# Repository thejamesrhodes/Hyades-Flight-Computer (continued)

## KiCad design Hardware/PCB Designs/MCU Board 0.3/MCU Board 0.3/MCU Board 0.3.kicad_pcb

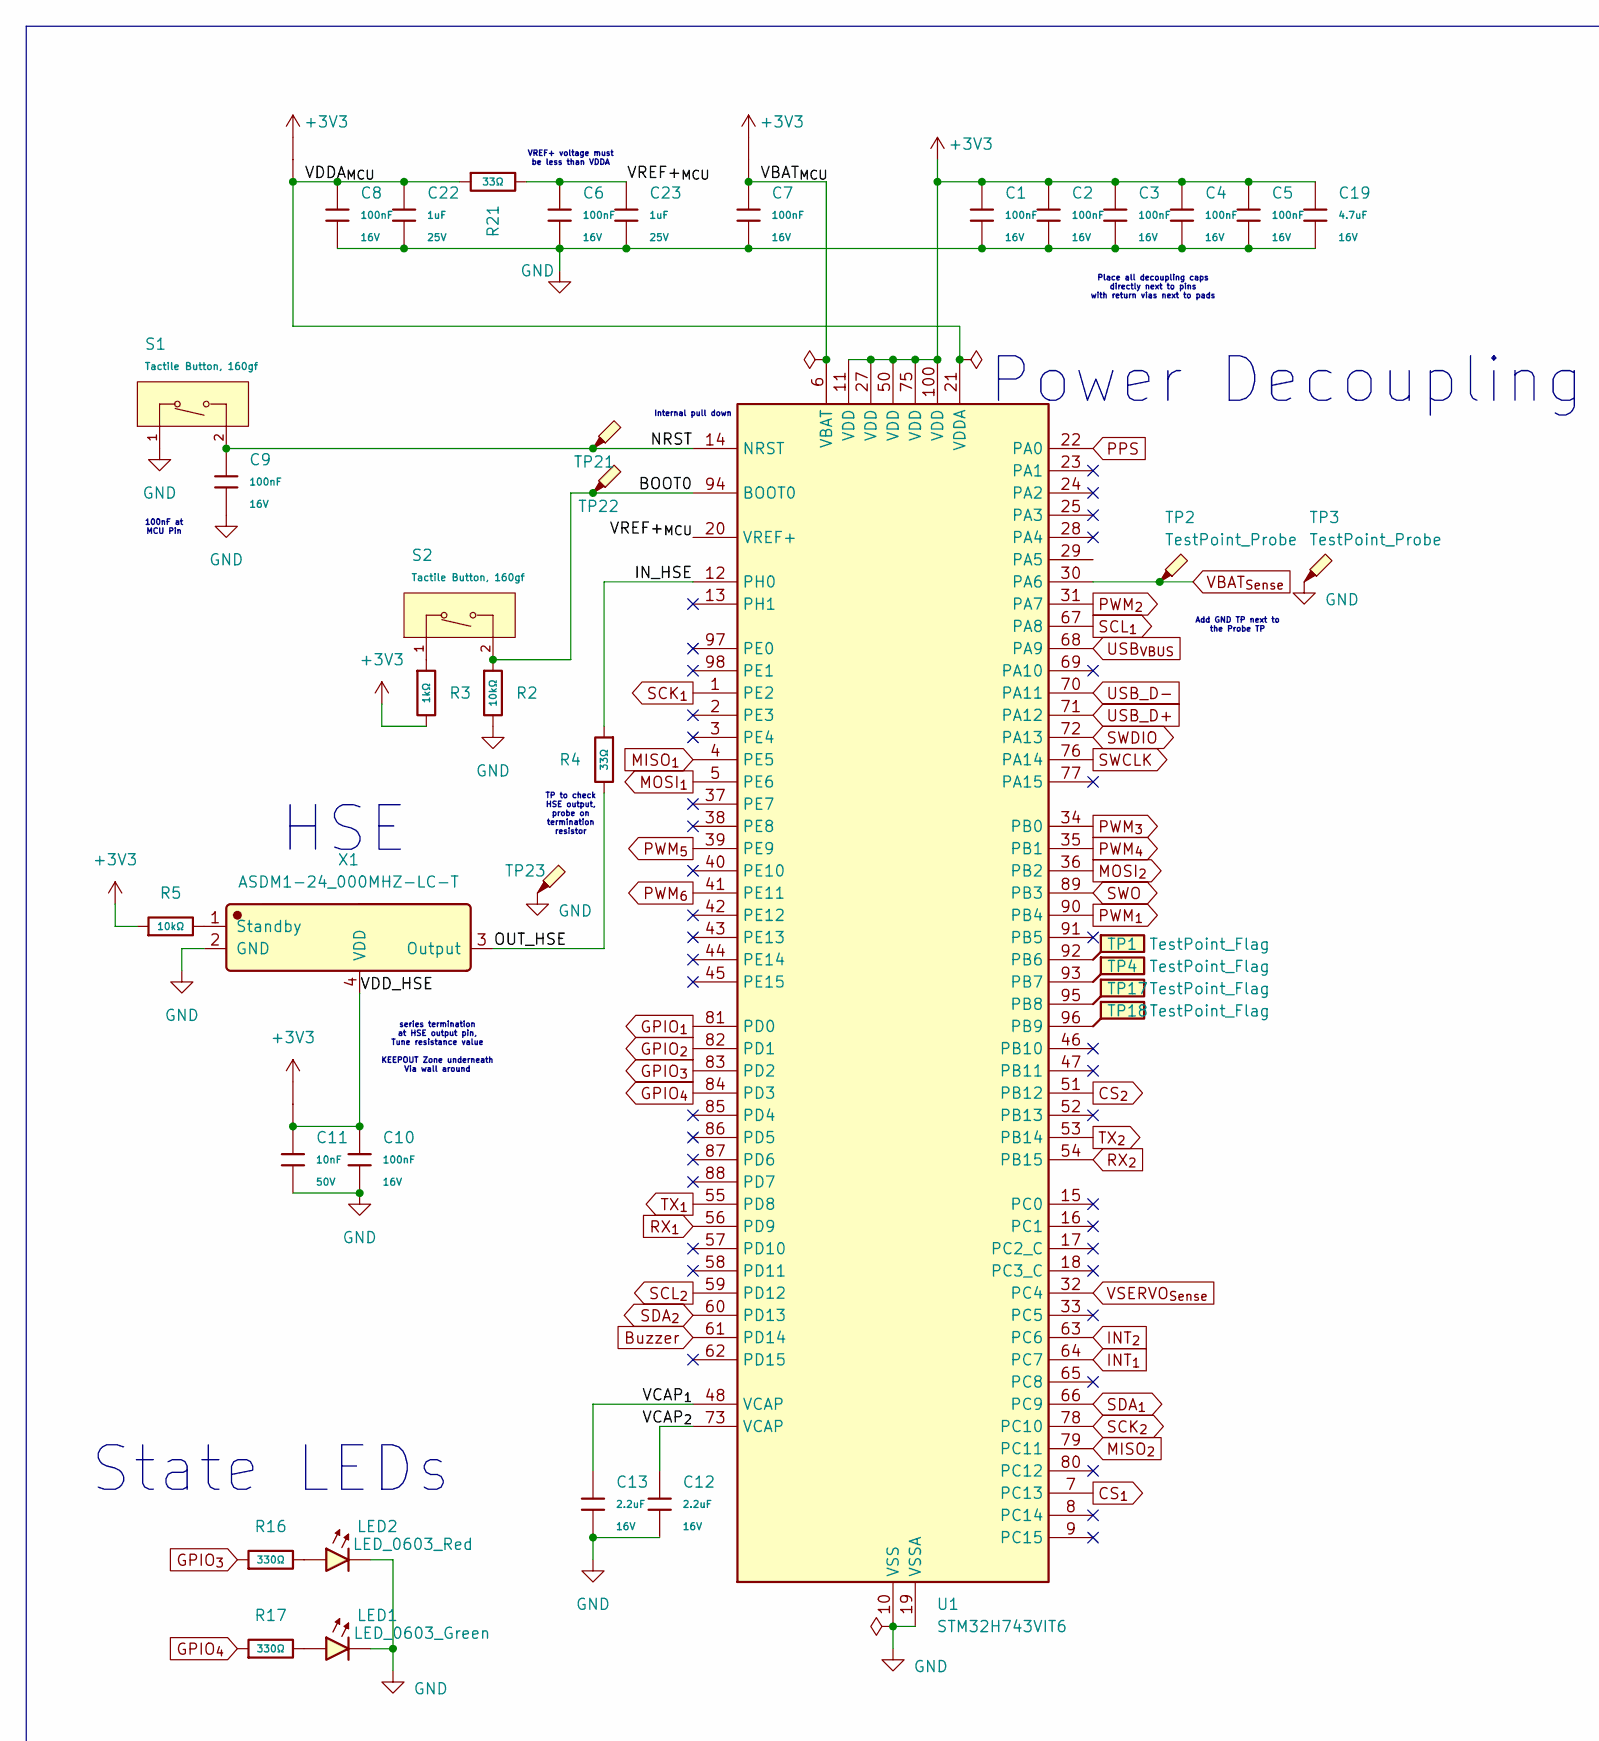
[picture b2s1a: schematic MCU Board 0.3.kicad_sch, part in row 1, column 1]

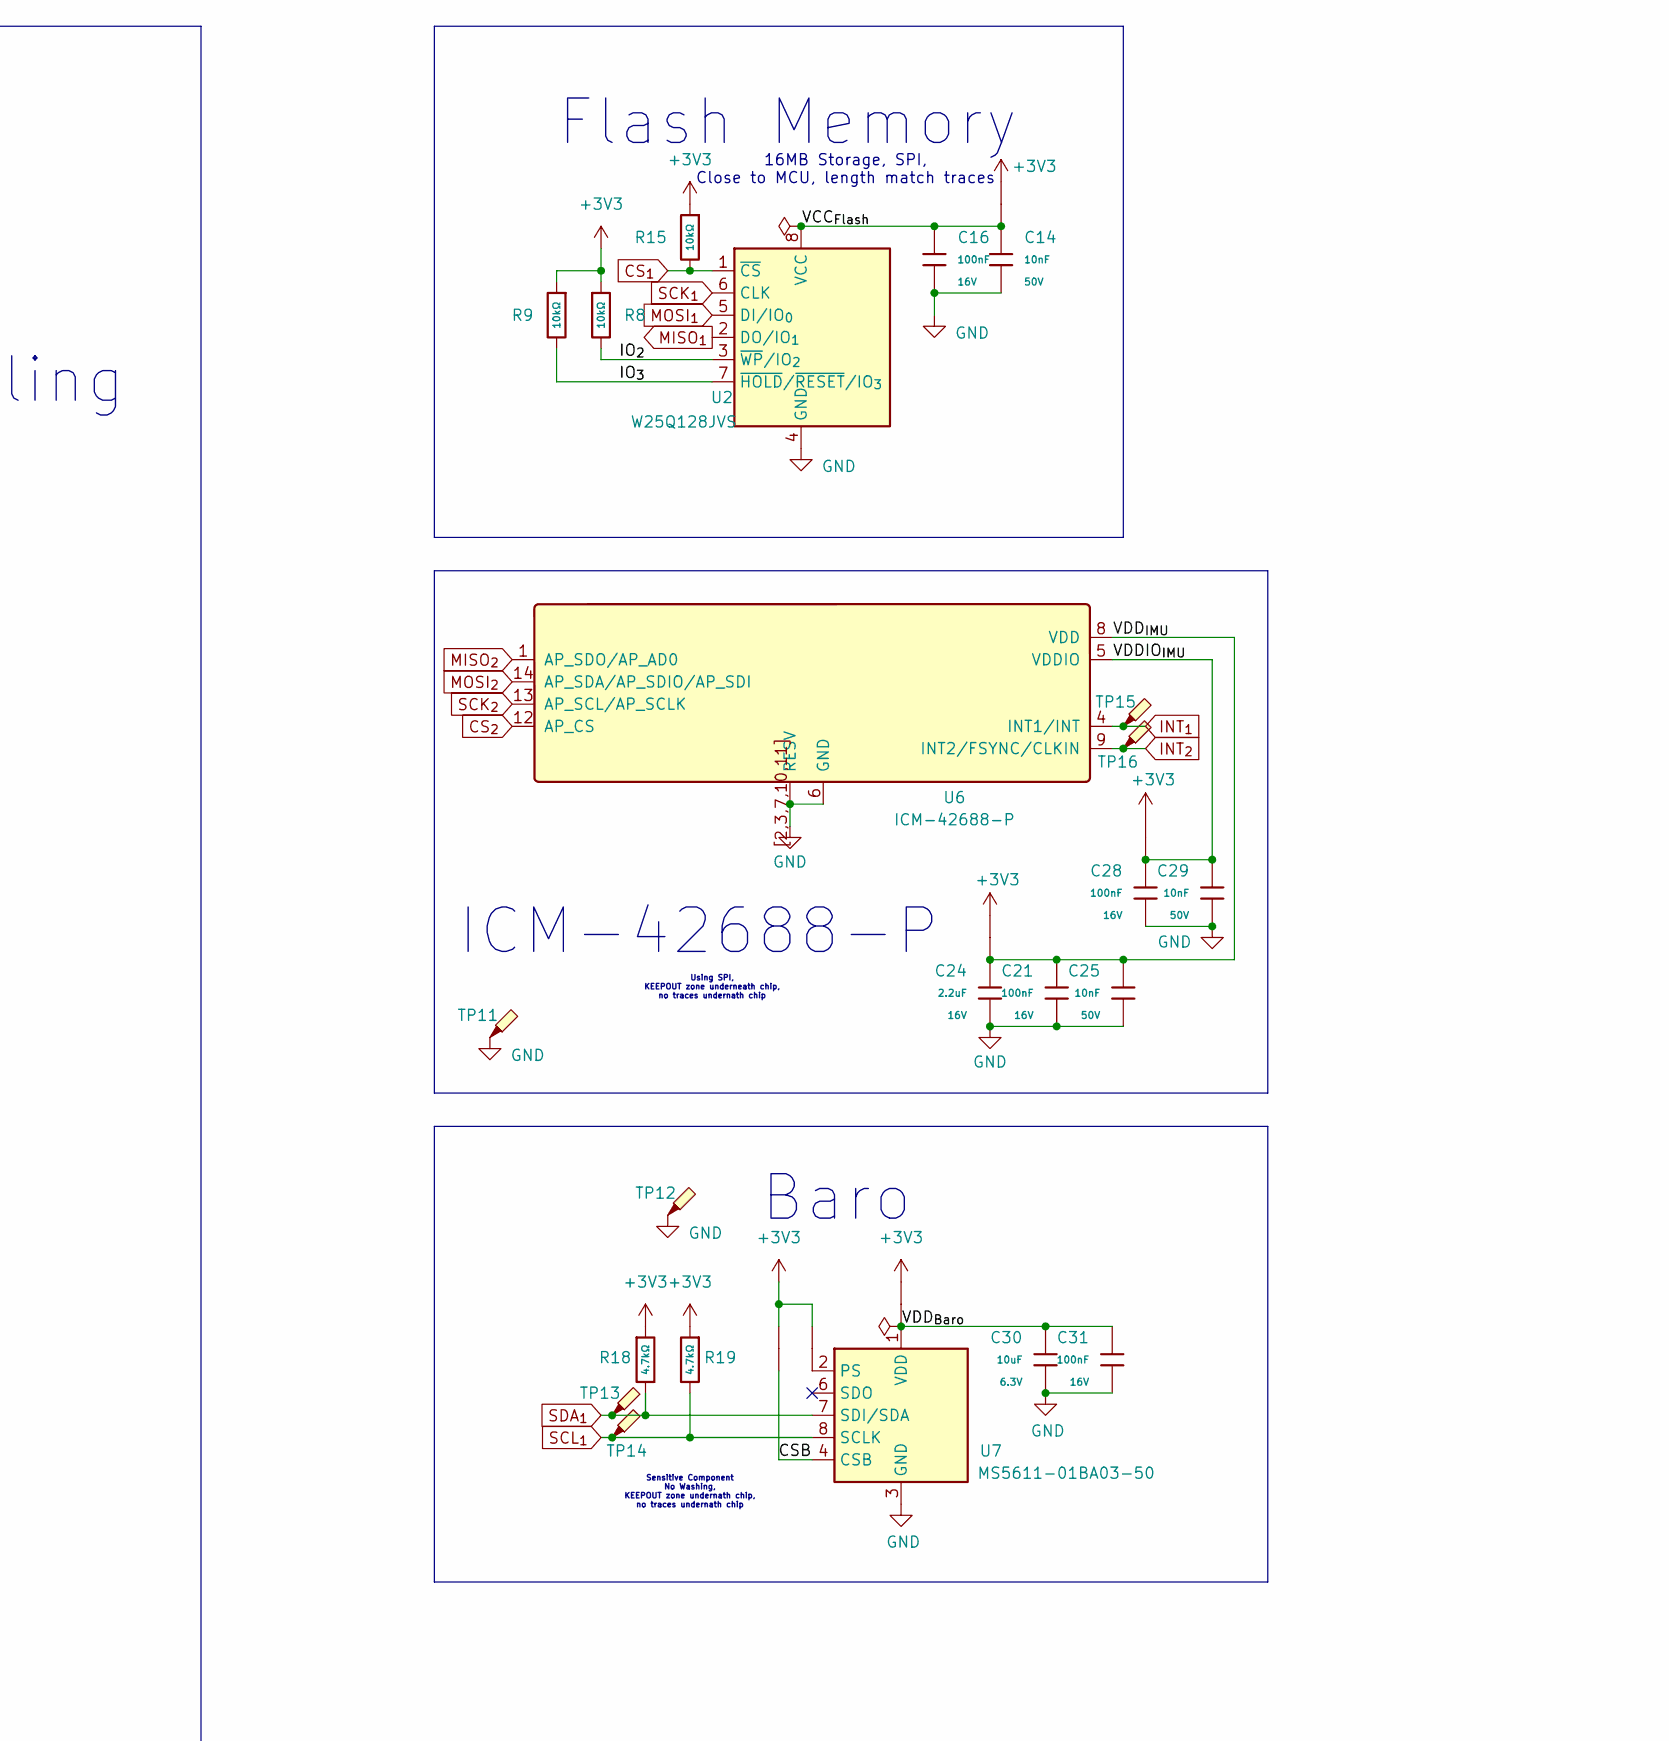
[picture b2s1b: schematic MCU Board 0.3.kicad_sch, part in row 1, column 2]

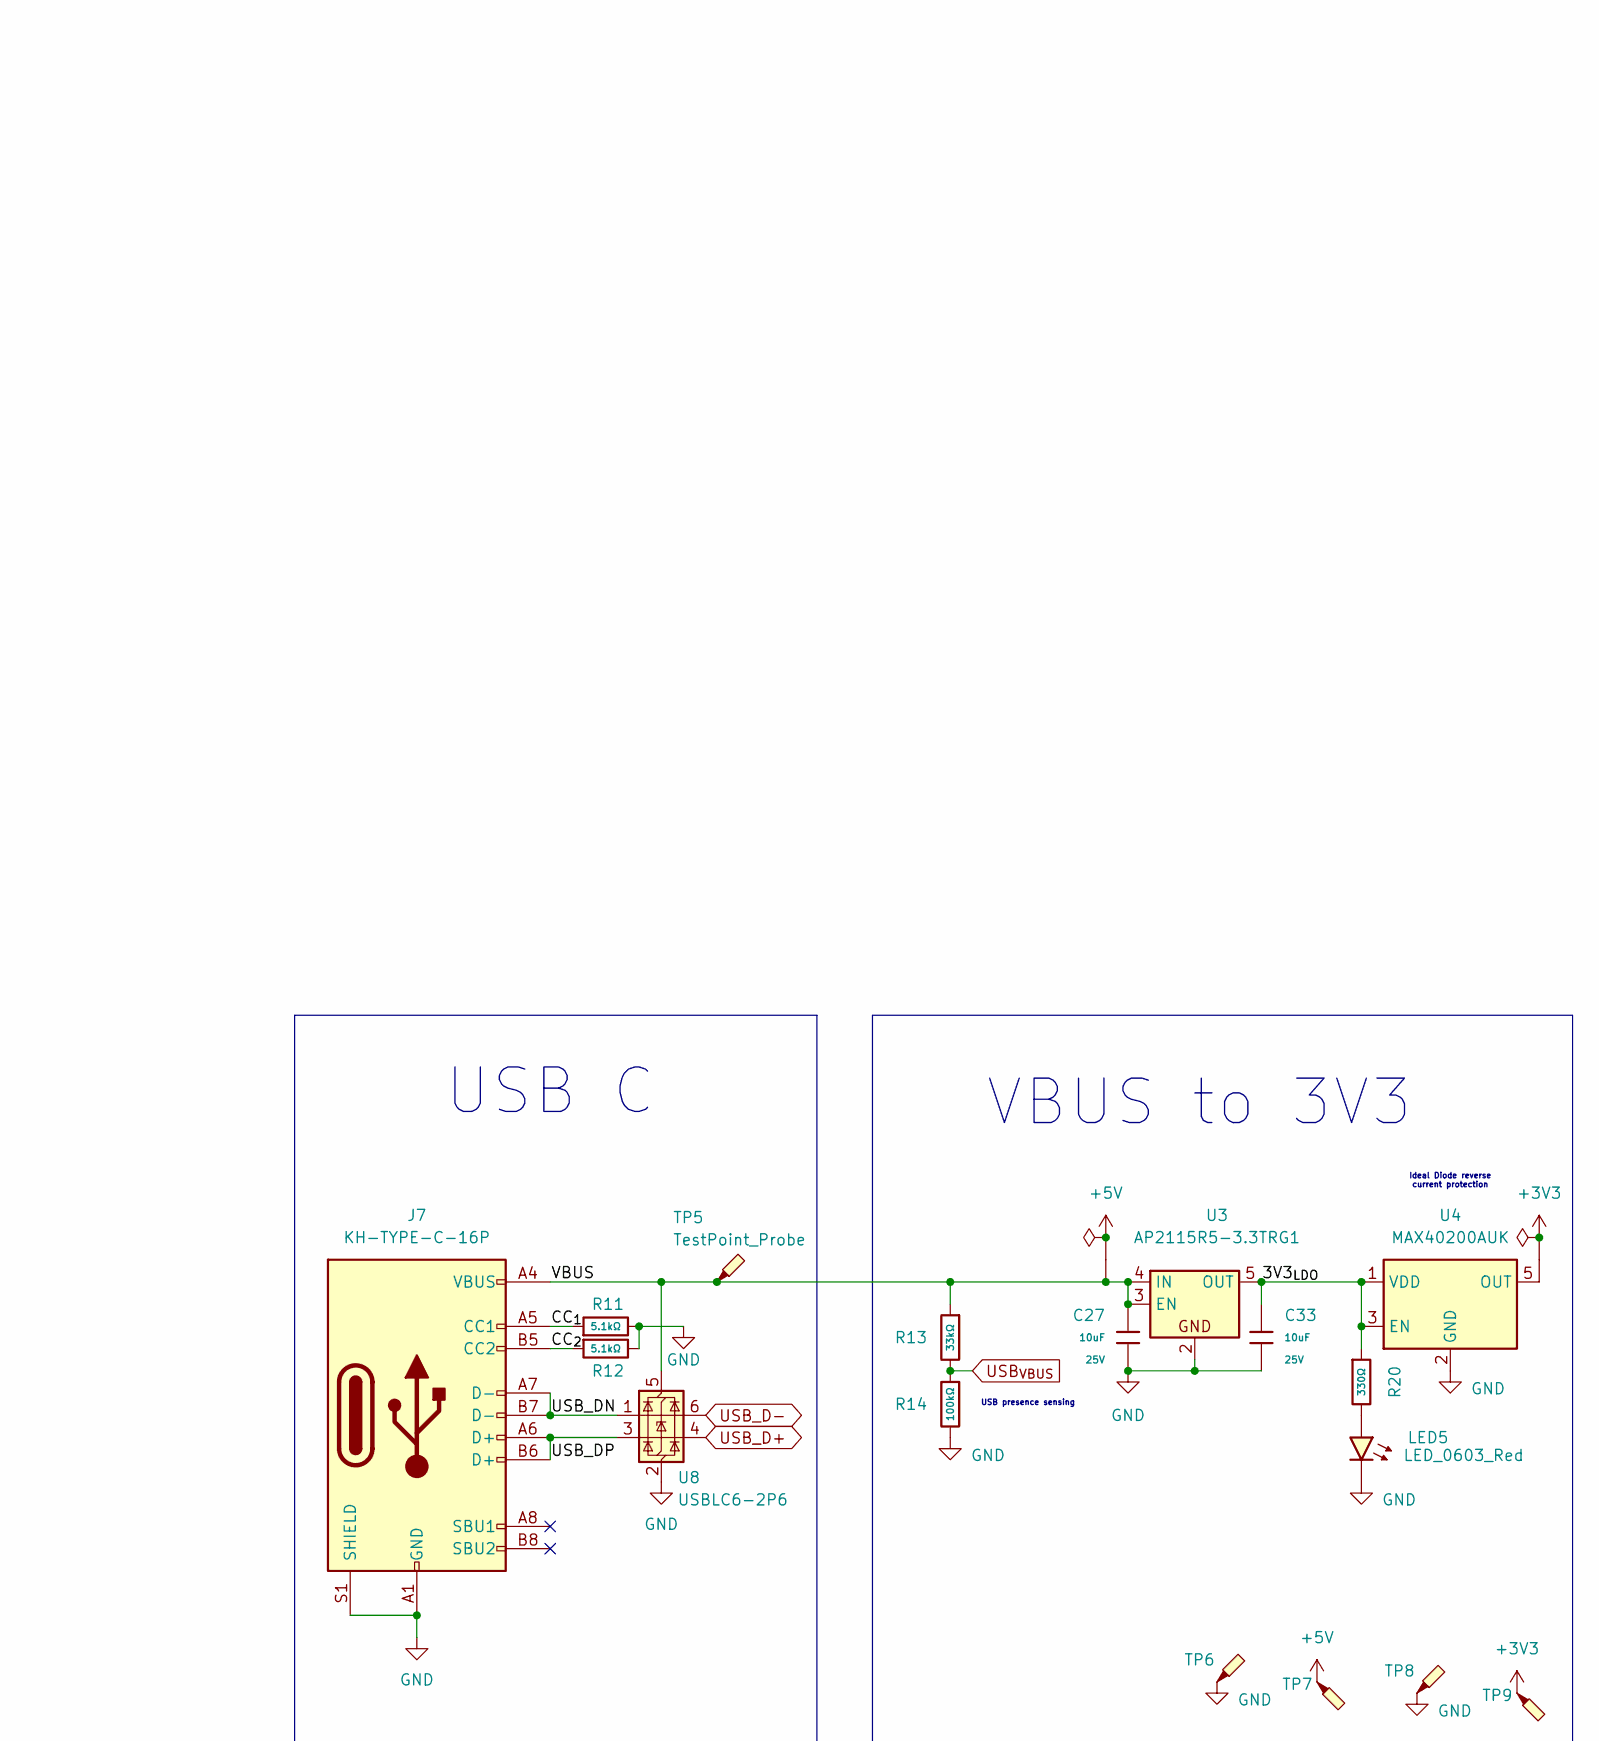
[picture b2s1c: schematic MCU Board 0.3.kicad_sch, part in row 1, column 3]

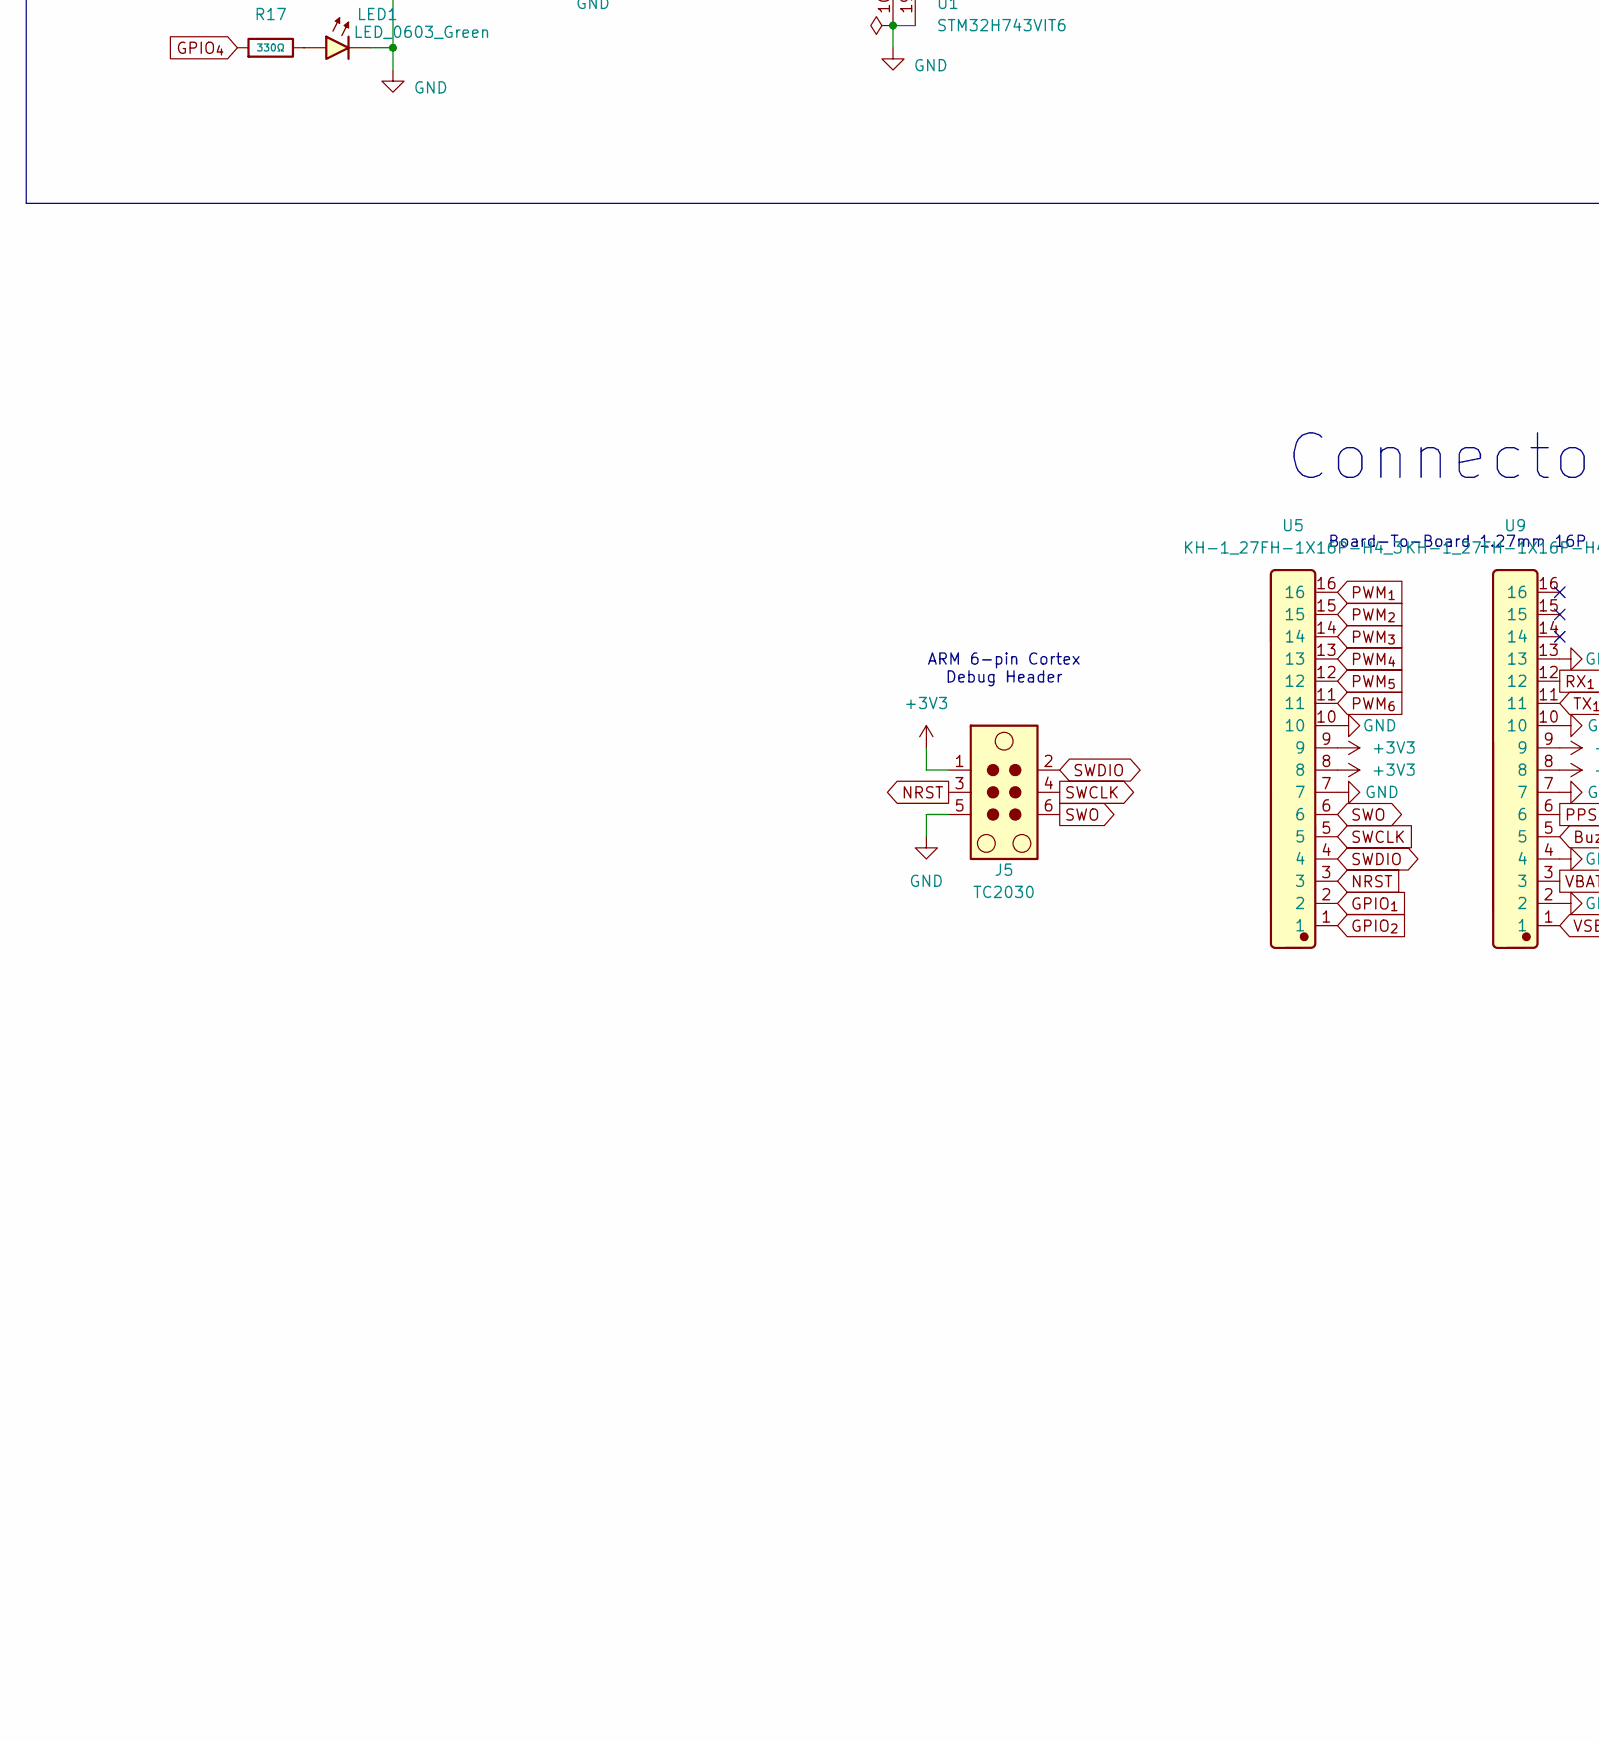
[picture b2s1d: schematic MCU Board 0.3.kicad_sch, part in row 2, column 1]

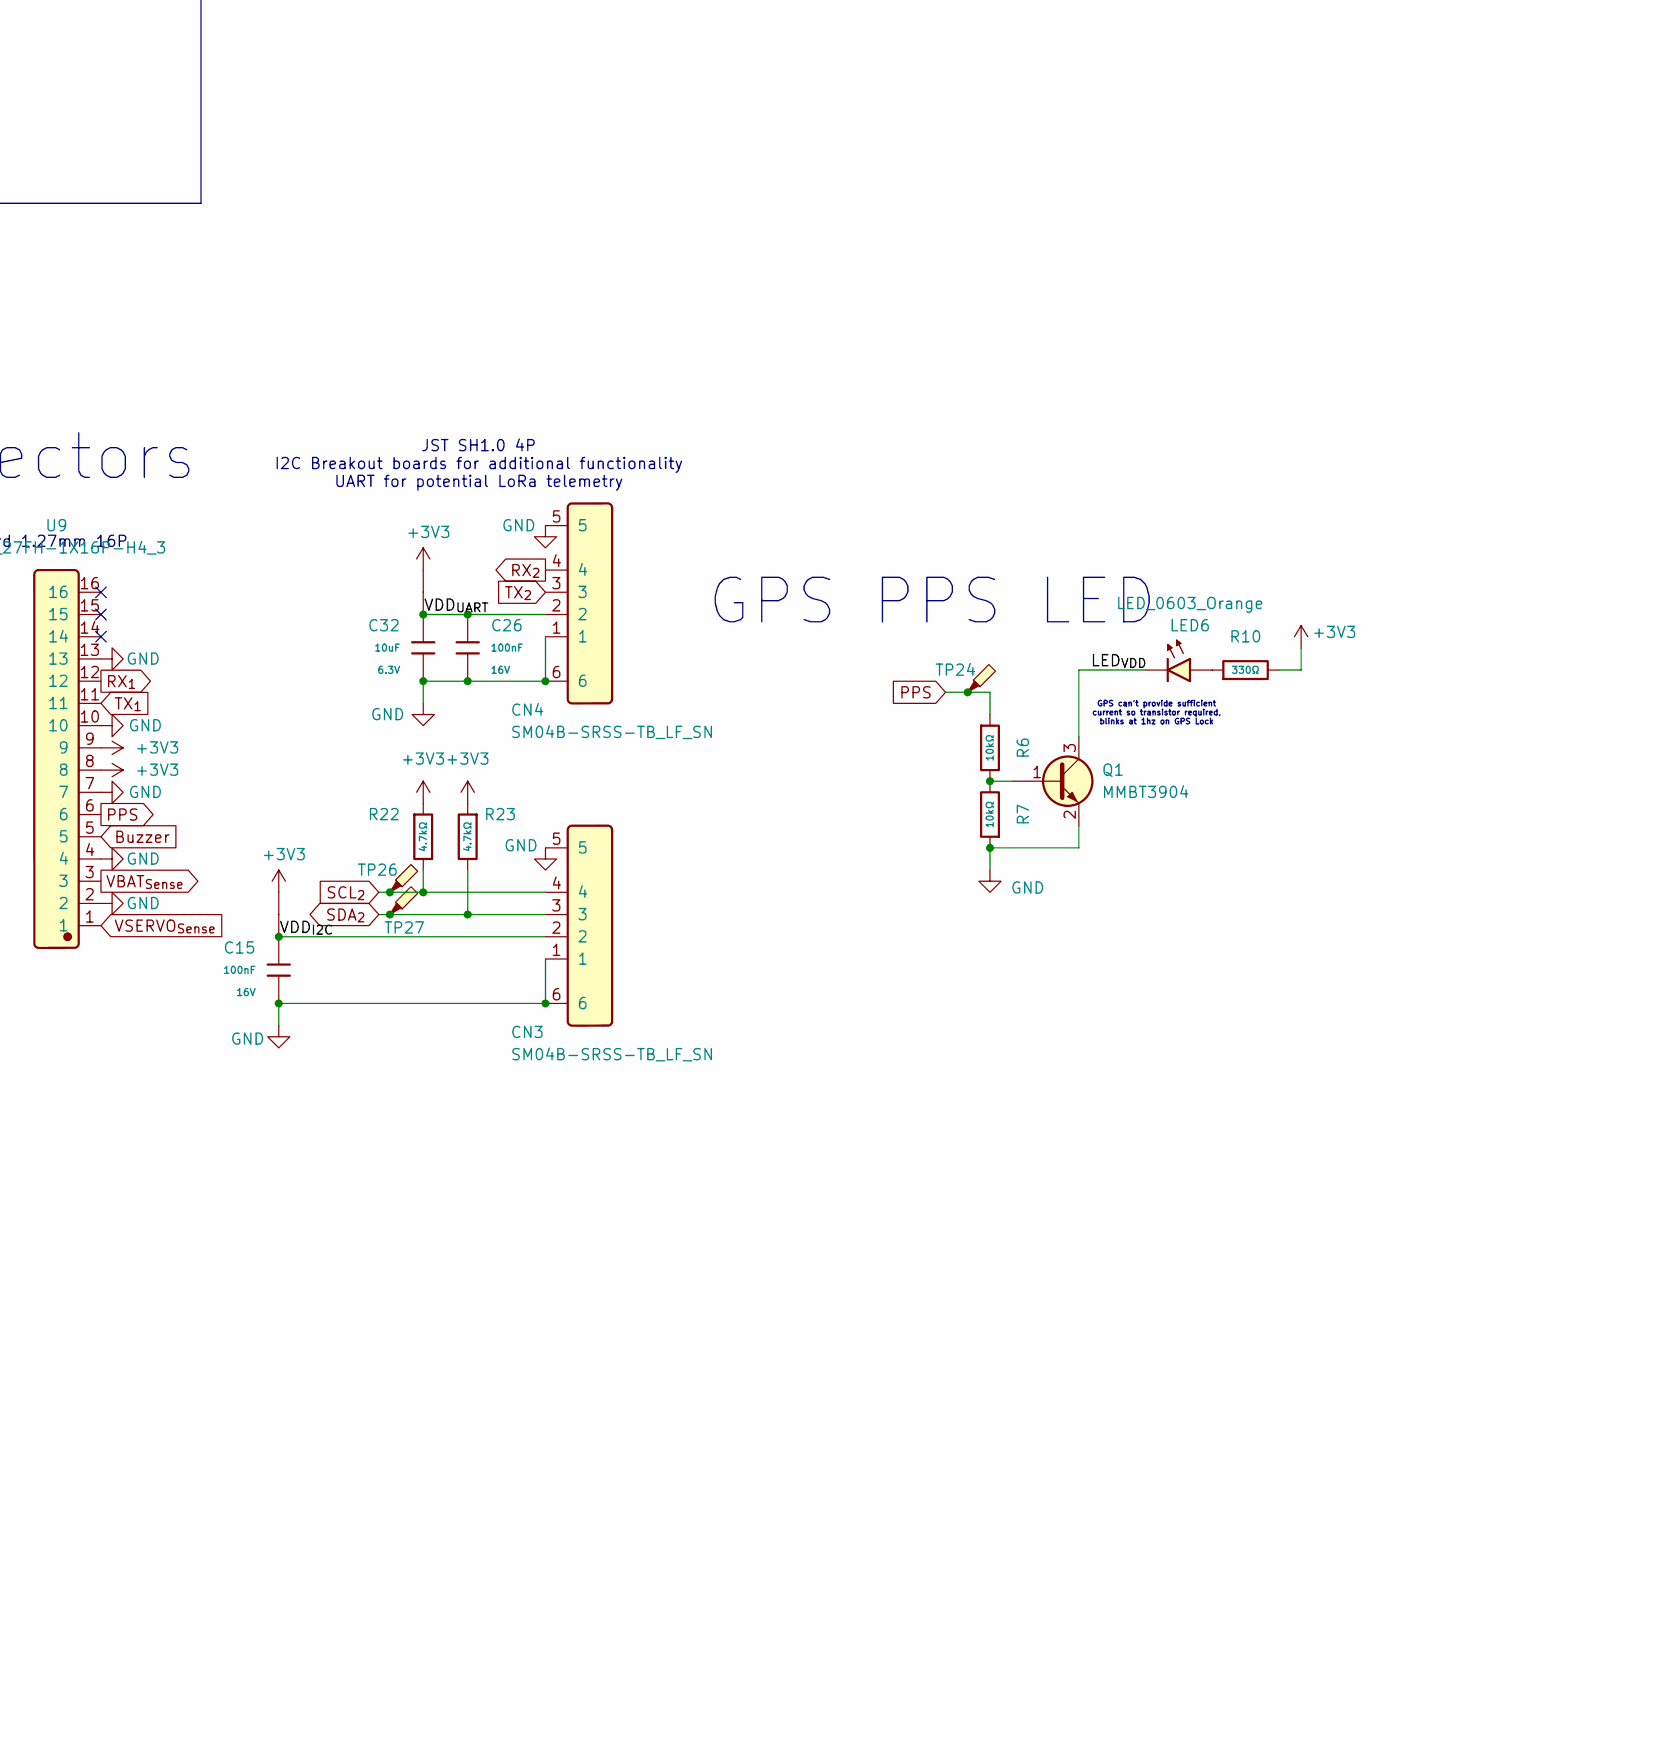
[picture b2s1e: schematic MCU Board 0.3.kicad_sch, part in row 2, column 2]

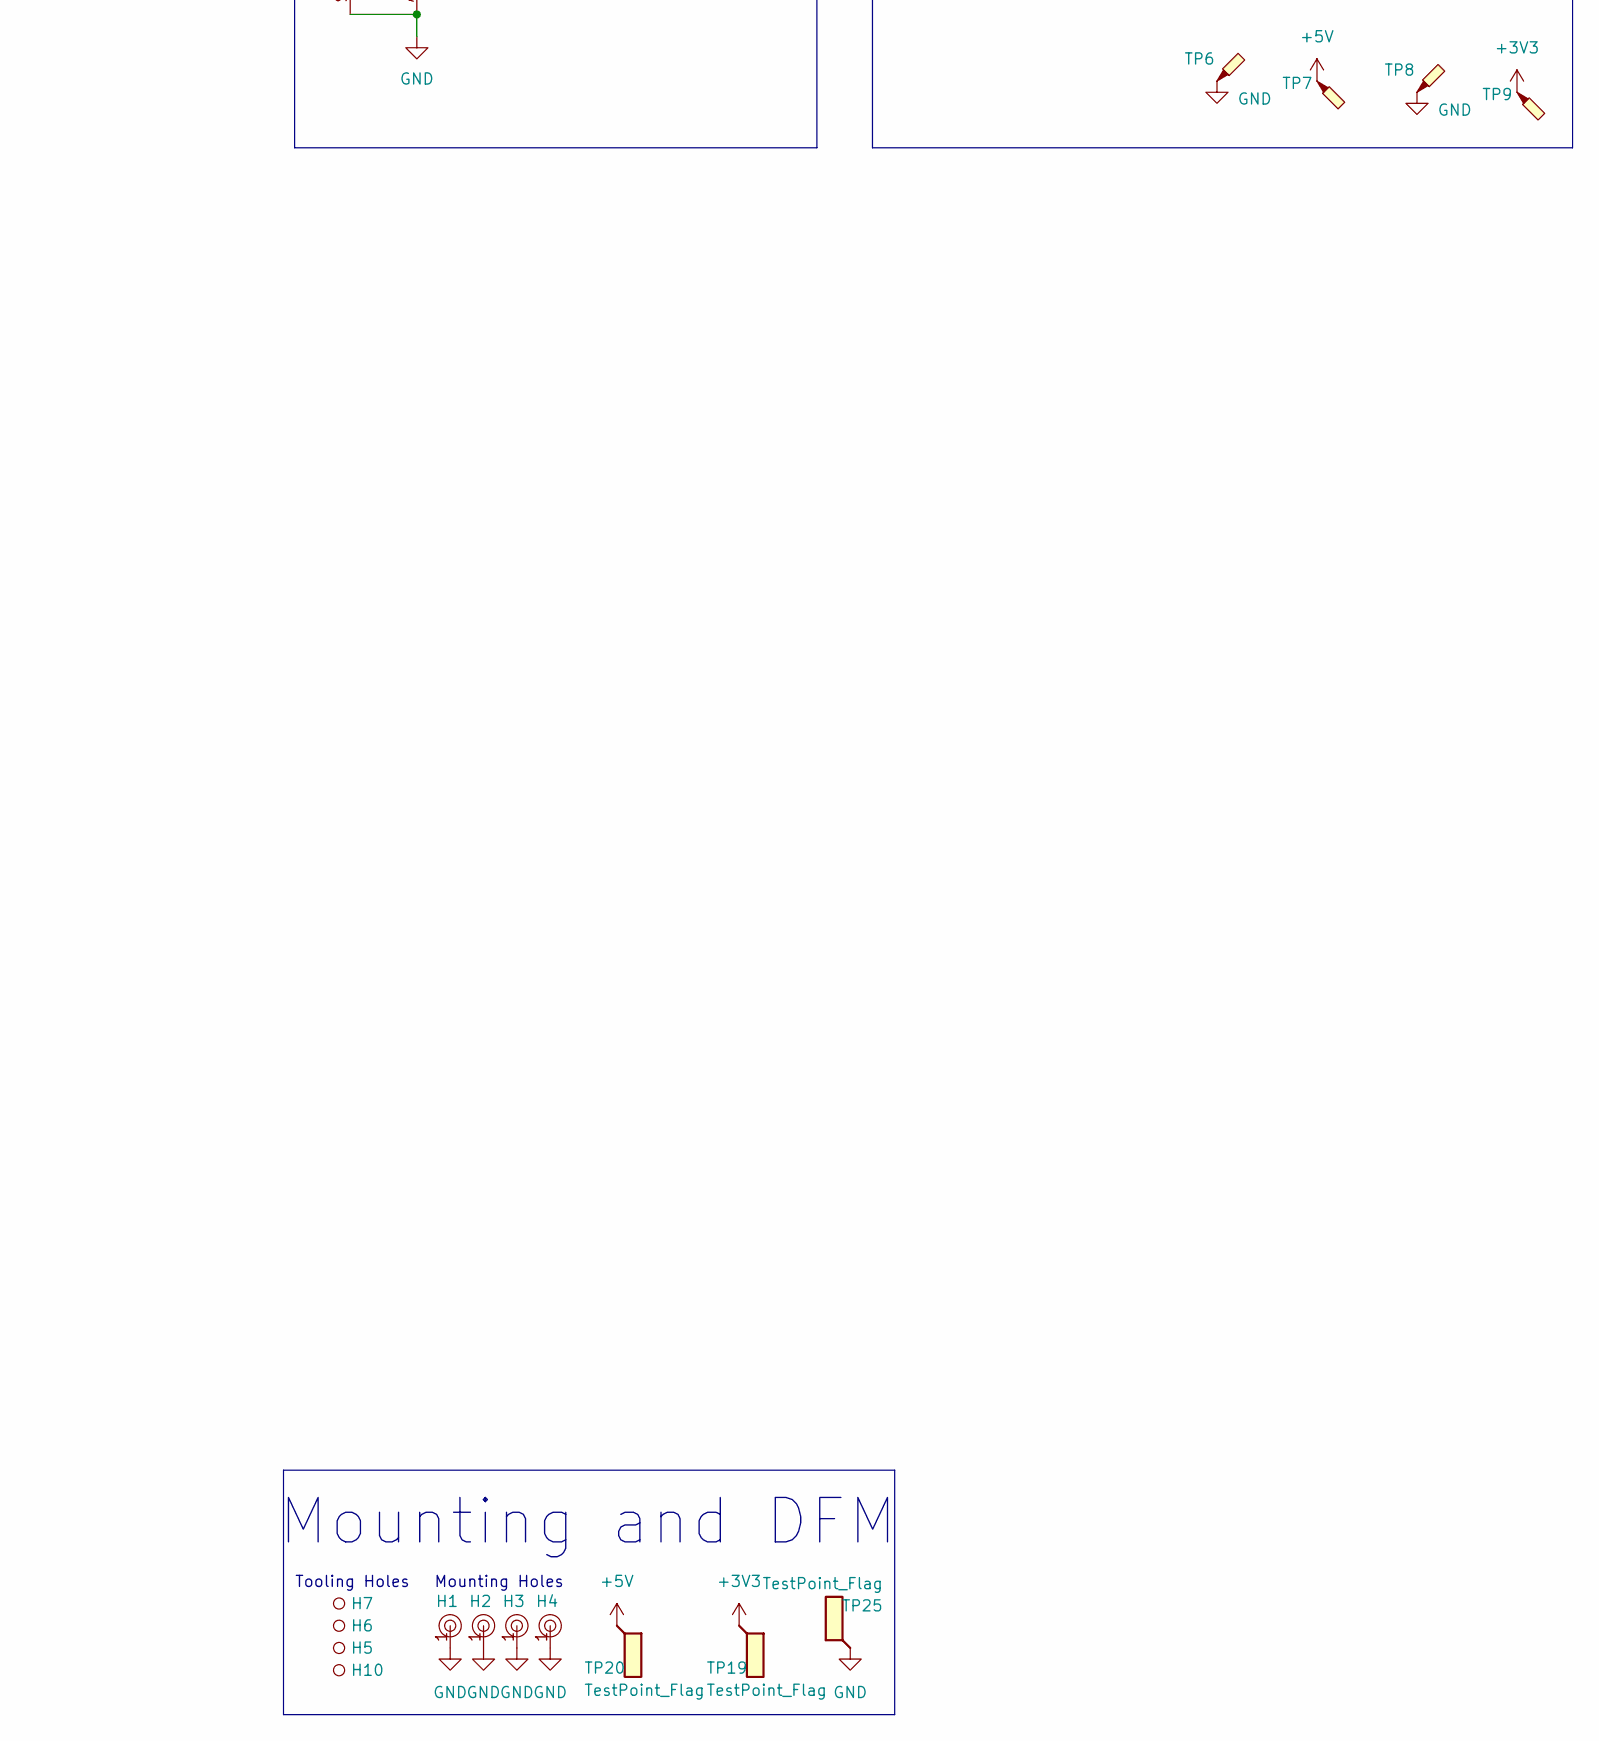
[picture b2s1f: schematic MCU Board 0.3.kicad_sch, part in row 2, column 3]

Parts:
C1, C2, C3, C4, C5, C6, C7, C8, C9, C10, C15, C16, C21, C26, C28, C31: 100nF; C_0402; Voltage Rated 16V; Tolerance ±10%; Part CL05B104KO5NNNC; LCSC C1525
C11, C14, C25, C29: 10nF; C_0402; Voltage Rated 50V; Tolerance ±10%; Part CL05B103KB5NNNC; LCSC C15195
C12, C13, C24: 2.2uF; C_0603; Voltage Rated 16V; Tolerance ±10%; Part CL10A225KO8NNNC; LCSC C23630
C19: 4.7uF; C_0603; Voltage Rated 16V; Tolerance ±10%; Part CL10A475KO8NNNC; LCSC C19666
C22, C23: 1uF; C_0402; Voltage Rated 25V; Tolerance ±10%; Part CL05A105KA5NQNC; LCSC C52923
C27, C33: 10uF; C_0805; Voltage Rated 25V; Tolerance ±10%; Part CL21A106KAYNNNE; LCSC C15850
C30, C32: 10uF; C_0402; Voltage Rated 6.3V; Tolerance ±20%; Part CL05A106MQ5NUNC; LCSC C15525
CN3, CN4: SM04B-SRSS-TB_LF_SN; JST_SH_SM04B-SRSS-TB_1x04-1MP_P1.00mm_Horizontal; Manufacturer Part SM04B-SRSS-TB(LF)(SN); LCSC C160404
H1, H2, H3, H4: Hole, 3mm
H5, H6, H7, H10: Hole_Tooling_JLCPCB
J5: TC2030; Tag-Connect_TC2030-IDC-NL_2x03_P1.27mm_Vertical
J7: KH-TYPE-C-16P; USB_C_Receptacle_GCT_USB4105-xx-A_16P_TopMnt_Horizontal
LED1: LED_0603_Green; LED_0603_1608Metric
LED2, LED5: LED_0603_Red; LED_0603_1608Metric
LED6: LED_0603_Orange; LED_0603_1608Metric
Q1: MMBT3904; SOT-23
R2, R5, R6, R7, R8, R9, R15: 10kΩ; R_0402; Overload Voltage (Max) 50V; Tolerance ±1%; Part 0402WGF1002TCE; LCSC C25744
R3: 1kΩ; R_0402; Overload Voltage (Max) 50V; Tolerance ±1%; Part 0402WGF1001TCE; LCSC C11702
R4, R21: 33Ω; R_0402; Overload Voltage (Max) 50V; Tolerance ±1%; Part 0402WGF330JTCE; LCSC C25105
R10, R16, R17, R20: 330Ω; R_0402; Overload Voltage (Max) 50V; Tolerance ±1%; Part 0402WGF3300TCE; LCSC C25104
R11, R12: 5.1kΩ; R_0402; Overload Voltage (Max) 50V; Tolerance ±1%; Part 0402WGF5101TCE; LCSC C25905
R13: 33kΩ; R_0402; Overload Voltage (Max) 50V; Tolerance ±1%; Part 0402WGF3302TCE; LCSC C25779
R14: 100kΩ; R_0402; Overload Voltage (Max) 50V; Tolerance ±1%; Part 0402WGF1003TCE; LCSC C25741
R18, R19, R22, R23: 4.7kΩ; R_0402; Overload Voltage (Max) 50V; Tolerance ±1%; Part 0402WGF4701TCE; LCSC C25900
S1, S2: Tactile Button, 160gf; SW_TS-1088-AR02016; Voltage Rating (Dc) 12V; Part TS-1088-AR02016; LCSC C720477
TIE1, TIE3, TIE4, TIE5, TIE6, TIE7, TIE8, TIE9, TIE10, TIE11, TIE12, TIE13, TIE14: NetTie; JUMPER_SMD_1x2_tiny_shorted; Part Number Do Not Place
TP1, TP4, TP17, TP18: TestPoint_Flag; TestPoint_Pad_04
TP2, TP3, TP5, TP6, TP7, TP8, TP9, TP11, TP12, TP13, TP14, TP15, TP16, TP21, TP22, TP23, TP24, TP26, TP27: TestPoint_Probe; TestPoint_Pad_04
TP19, TP20, TP25: TestPoint_Flag; SolderWirePad_1x01_SMD_2x4mm
U1: STM32H743VIT6; LQFP-100_14x14mm_P0.5mm
U2: W25Q128JVS; SOIC-8_5.3x5.3mm_P1.27mm
U3: AP2115R5-3.3TRG1; Diodes_SOT-89-5; LCSC 460316
U4: MAX40200AUK; SOT-23-5
U5, U9: KH-1_27FH-1X16P-H4_3; Manufacturer Part KH-1.27FH-1X16P-H4.3; LCSC C2938387
U6: ICM-42688-P; Manufacturer Part ICM-42688-P; LCSC C1850418
U7: MS5611-01BA03-50; LGA-8_3x5mm_P1.25mm
U8: USBLC6-2P6; SOT-666
X1: ASDM1-24_000MHZ-LC-T; OSC-SMD_4P-L3.2-W2.5-BL; Manufacturer Part ASDM1-24.000MHZ-LC-T; LCSC C1987235

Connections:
+3V3: C1.1, C2.1, C3.1, C4.1, C5.1, C19.1, J5.1, R3.2, R5.1, R8.1, R9.1, R10.2, R15.1, R18.1, R19.1, R22.1, R23.1, TIE1.2, TIE3.2, TIE4.2, TIE5.2, TIE6.2, TIE7.2, TIE9.2, TIE10.2, TIE11.2, TIE12.2, TIE13.2, TIE14.2, TP9.1 (1_1), TP19.1 (1_1), U1.11 (VDD), U1.27 (VDD), U1.50 (VDD), U1.75 (VDD), U1.100 (VDD), U5.8, U5.9, U9.8, U9.9
+5V: TIE8.2, TP7.1 (1_1), TP20.1 (1_1)
/3V3_{LDO}: C33.1, R20.1, U3.5 (OUT), U4.1 (VDD), U4.3 (EN)
/BOOT0: R2.1, S2.2 (B), TP22.1 (1_1), U1.94 (BOOT0)
/CC_{1}: J7.A5 (CC1), R11.1
/CC_{2}: J7.B5 (CC2), R12.1
/CSB: TIE14.1, U7.4 (CSB), U7.5 (CSB)
/IN_HSE: R4.1, U1.12 (PH0)
/IO_{2}: R8.2, U2.3 (~WP/IO_{2})
/IO_{3}: R9.2, U2.7 (~HOLD/~RESET/IO_{3})
/LED_{VDD}: LED6.1 (K), Q1.3 (C)
/OUT_HSE: R4.2, X1.3 (Output)
/USB_DN: J7.A7 (D-), J7.B7 (D-), U8.1 (I/O1)
/USB_DP: J7.A6 (D+), J7.B6 (D+), U8.3 (I/O2)
/VBAT_{MCU}: C7.1, TIE1.1, U1.6 (VBAT)
/VBUS: C27.1, J7.A4 (VBUS), J7.A9 (VBUS), J7.B4 (VBUS), J7.B9 (VBUS), R13.1, TIE8.1, TP5.1 (1_1), U3.3 (EN), U3.4 (IN), U8.5 (VBUS)
/VCAP_{1}: C13.1, U1.48 (VCAP)
/VCAP_{2}: C12.1, U1.73 (VCAP)
/VCC_{Flash}: C14.1, C16.1, TIE5.1, U2.8 (VCC)
/VDDA_{MCU}: C8.1, C22.1, R21.1, TIE3.1, U1.21 (VDDA)
/VDDIO_{IMU}: C28.1, C29.1, TIE6.1, U6.5 (VDDIO)
/VDD_HSE: C10.1, C11.1, TIE4.1, X1.4 (VDD)
/VDD_{Baro}: C30.1, C31.1, TIE12.1, U7.1 (VDD)
/VDD_{I2C}: C15.1, CN3.2, TIE11.1
/VDD_{IMU}: C21.1, C24.1, C25.1, TIE7.1, U6.8 (VDD)
/VDD_{UART}: C26.1, C32.1, CN4.2, TIE10.1
/VREF+_{MCU}: C6.1, C23.1, R21.2, U1.20 (VREF+)
Buzzer: U1.61 (PD14), U9.5
CS_{1}: R15.2, U1.7 (PC13), U2.1 (~CS)
CS_{2}: U1.51 (PB12), U6.12 (AP_CS)
GND: C1.2, C2.2, C3.2, C4.2, C5.2, C6.2, C7.2, C8.2, C9.2, C10.2, C11.2, C12.2, C13.2, C14.2, C15.2, C16.2, C19.2, C21.2, C22.2, C23.2, C24.2, C25.2, C26.2, C27.2, C28.2, C29.2, C30.2, C31.2, C32.2, C33.2, CN3.1, CN3.5, CN3.6, CN4.1, CN4.5, CN4.6, H1.1, H2.1, H3.1, H4.1, J5.5, J7.A1 (GND), J7.A12 (GND), J7.B1 (GND), J7.B12 (GND), J7.S1 (SHIELD), LED1.1 (K), LED2.1 (K), LED5.1 (K), Q1.2 (E), R2.2, R7.1, R11.2, R12.2, R14.2, S1.1 (A), TP3.1 (1_1), TP6.1 (1_1), TP8.1 (1_1), TP11.1 (1_1), TP12.1 (1_1), TP23.1 (1_1), TP25.1 (1_1), U1.10 (VSS), U1.19 (VSSA), U1.26 (VSS), U1.49 (VSS), U1.74 (VSS), U1.99 (VSS), U2.4 (GND), U3.2, U4.2 (GND), U5.7, U5.10, U6.2 (RESV), U6.3 (RESV), U6.6 (GND), U6.7 (RESV), U6.10 (RESV), U6.11 (RESV), U6.[2,3,7,10,11] (RESV), U7.3 (GND), U8.2 (GND), U9.2, U9.4, U9.7, U9.10, U9.13, X1.2 (GND)
GPIO_{1}: U1.81 (PD0), U5.2
GPIO_{2}: U1.82 (PD1), U5.1
GPIO_{3}: R16.1, U1.83 (PD2)
GPIO_{4}: R17.1, U1.84 (PD3)
INT_{1}: TP15.1 (1_1), U1.64 (PC7), U6.4 (INT1/INT)
INT_{2}: TP16.1 (1_1), U1.63 (PC6), U6.9 (INT2/FSYNC/CLKIN)
MISO_{1}: U1.4 (PE5), U2.2 (DO/IO_{1})
MISO_{2}: U1.79 (PC11), U6.1 (AP_SDO/AP_AD0)
MOSI_{1}: U1.5 (PE6), U2.5 (DI/IO_{0})
MOSI_{2}: U1.36 (PB2), U6.14 (AP_SDA/AP_SDIO/AP_SDI)
NRST: C9.1, J5.3, S1.2 (B), TP21.1 (1_1), U1.14 (NRST), U5.3
unnamed: LED1.2 (A), R17.2
unnamed: LED2.2 (A), R16.2
unnamed: LED5.2 (A), R20.2
unnamed: LED6.2 (A), R10.1
unnamed: Q1.1 (B), R6.2, R7.2
unnamed: R3.1, S2.1 (A)
unnamed: TP1.1 (1_1), U1.92 (PB6)
unnamed: TP4.1 (1_1), U1.93 (PB7)
unnamed: TP17.1 (1_1), U1.95 (PB8)
unnamed: TP18.1 (1_1), U1.96 (PB9)
unnamed: TIE9.1, U4.5 (OUT)
unnamed: TIE13.1, U7.2 (PS)
unnamed: R5.2, X1.1 (Standby)
PPS: R6.1, TP24.1 (1_1), U1.22 (PA0), U9.6
PWM_{1}: U1.90 (PB4), U5.16
PWM_{2}: U1.31 (PA7), U5.15
PWM_{3}: U1.34 (PB0), U5.14
PWM_{4}: U1.35 (PB1), U5.13
PWM_{5}: U1.39 (PE9), U5.12
PWM_{6}: U1.41 (PE11), U5.11
RX_{1}: U1.56 (PD9), U9.12
RX_{2}: CN4.4, U1.54 (PB15)
SCK_{1}: U1.1 (PE2), U2.6 (CLK)
SCK_{2}: U1.78 (PC10), U6.13 (AP_SCL/AP_SCLK)
SCL_{1}: R19.2, TP14.1 (1_1), U1.67 (PA8), U7.8 (SCLK)
SCL_{2}: CN3.4, R22.2, TP26.1 (1_1), U1.59 (PD12)
SDA_{1}: R18.2, TP13.1 (1_1), U1.66 (PC9), U7.7 (SDI/SDA)
SDA_{2}: CN3.3, R23.2, TP27.1 (1_1), U1.60 (PD13)
SWCLK: J5.4, U1.76 (PA14), U5.5
SWDIO: J5.2, U1.72 (PA13), U5.4
SWO: J5.6, U1.89 (PB3), U5.6
TX_{1}: U1.55 (PD8), U9.11
TX_{2}: CN4.3, U1.53 (PB14)
USB_D+: U1.71 (PA12), U8.4 (I/O2)
USB_D-: U1.70 (PA11), U8.6 (I/O1)
USB_{VBUS}: R13.2, R14.1, U1.68 (PA9)
VBAT_{Sense}: TP2.1 (1_1), U1.30 (PA6), U9.3
VSERVO_{Sense}: U1.32 (PC4), U9.1

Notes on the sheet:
Power Decoupling
Connectors
Mounting Holes
USB presence sensing
Using SPI, KEEPOUT zone underneath chip, no traces undernath chip
Baro
Flash Memory
Board-To-Board 1.27mm 16P
JST SH1.0 4P I2C Breakout boards for additional functionality UART for potential LoRa telemetry
16MB Storage, SPI, Close to MCU, length match traces
Sensitive Component No Washing, KEEPOUT zone undernath chip, no traces undernath chip
TP to check HSE output, probe on termination resistor
ICM-42688-P
Ideal Diode reverse current protection
VREF+ voltage must be less than VDDA
GPS can't provide sufficient current so transistor required, blinks at 1hz on GPS Lock
ARM 6-pin Cortex Debug Header
Place all decoupling caps directly next to pins with return vias next to pads
Internal pull down
GPS PPS LED
VBUS to 3V3
series termination at HSE output pin, Tune resistance value KEEPOUT Zone underneath Via wall around
100nF at MCU Pin
Tooling Holes
HSE
USB C
Mounting and DFM
Add GND TP next to the Probe TP
State LEDs

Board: 4 copper layers, 120 parts (0 on the bottom side), 80 nets, no tracks yet.
